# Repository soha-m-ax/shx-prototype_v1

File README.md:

# SHX // PROTOTYPE
### Designed by SohaMax // Solar Strike ⚡

The **SHX // PROTOTYPE** is a 6-keys & 1 rotary encloder macro pad designed for custom inputs.

---

## Visuals:

### 1. CAD View
The final assembly of the SHX PROTOTYPE keypad.

### 2. Schematic
The circuit diagram showing the XIAO RP2040 connected to the 7-key matrix.

### 3. PCB Layout
The custom 2-layer board design featuring hand-routed traces and mascot art.

---

## Bill of Materials (BOM):

| Component | Quantity | Purpose |
| :--- | :--- | :--- |
| **Seeed Studio XIAO RP2040** | 1 | Microcontroller |
| **Through-hole 1N4148 Diodes** | 7 | Signal Logic |
| **Mechanical Switches (MX-Style)** | 6 | Key Inputs |
| **EC11 Rotary Encoders** | 1 | Knob Inputs |
| **0.91 inch OLED Display** | 1 | Screen view |
| **DSA keycaps (White)** | 6 | Keycap Fit|
| **SK6812 MINI-E LEDs** | 7 | Custom lighting |
| **M3x16mm Screws** | 3 | | 3D Case Fiting |
| **M3x5mx4mm Heatset Inserts** | 3 | | 3D Case Fiting |
| **3D Printed Top Cover & Main Case** | Each 1 | Enclosure |

---

## Spec:

* **MCU:** XIAO RP2040.
* **Architecture:** 6 Mechanical Keys + 1 Rotary Encoder (Push-Button).
* **Firmware:** QMK (For now)
* **PCB Design:** KiCad 8.0.
* **CAD Design:** Fusion 360.

---

## Features:

The SHX // PROTOTYPE is configured with the following hardware & firmware capabilities:
* It's have  6 keys and 1 rotary encoder (press and rotate)
* It's have a display. At Starting it will show my branding and after some sec. it will show a bongocat, pressing a key make the cat's hand move (hope it work)
* Each key have each lights that can be glow brighter by pressing each key (each key make glow specific 1 light) and one exstra as side lighting...
---
> This firmware is not tested so i hope it will work... :-)

---

## Notes:
It will be nice to print all my 3d cash in yellow colour. (plz)

---

## Some bla bla:

I really happy to make this and also learned many things like codes etc for keyboard's farmware and also software like kicad, Fusion 360 etc. It's my first project with microcontroller. At first I couldn't understand anything but slow slow i learnet many more from internet. Hope everyone like it!
## Thanks hack club to give me a chance to show my skills and waiting! to make it real. I will make many more things!!...

 * {\\__/} 
* ( • . •) 
*  / >♥️

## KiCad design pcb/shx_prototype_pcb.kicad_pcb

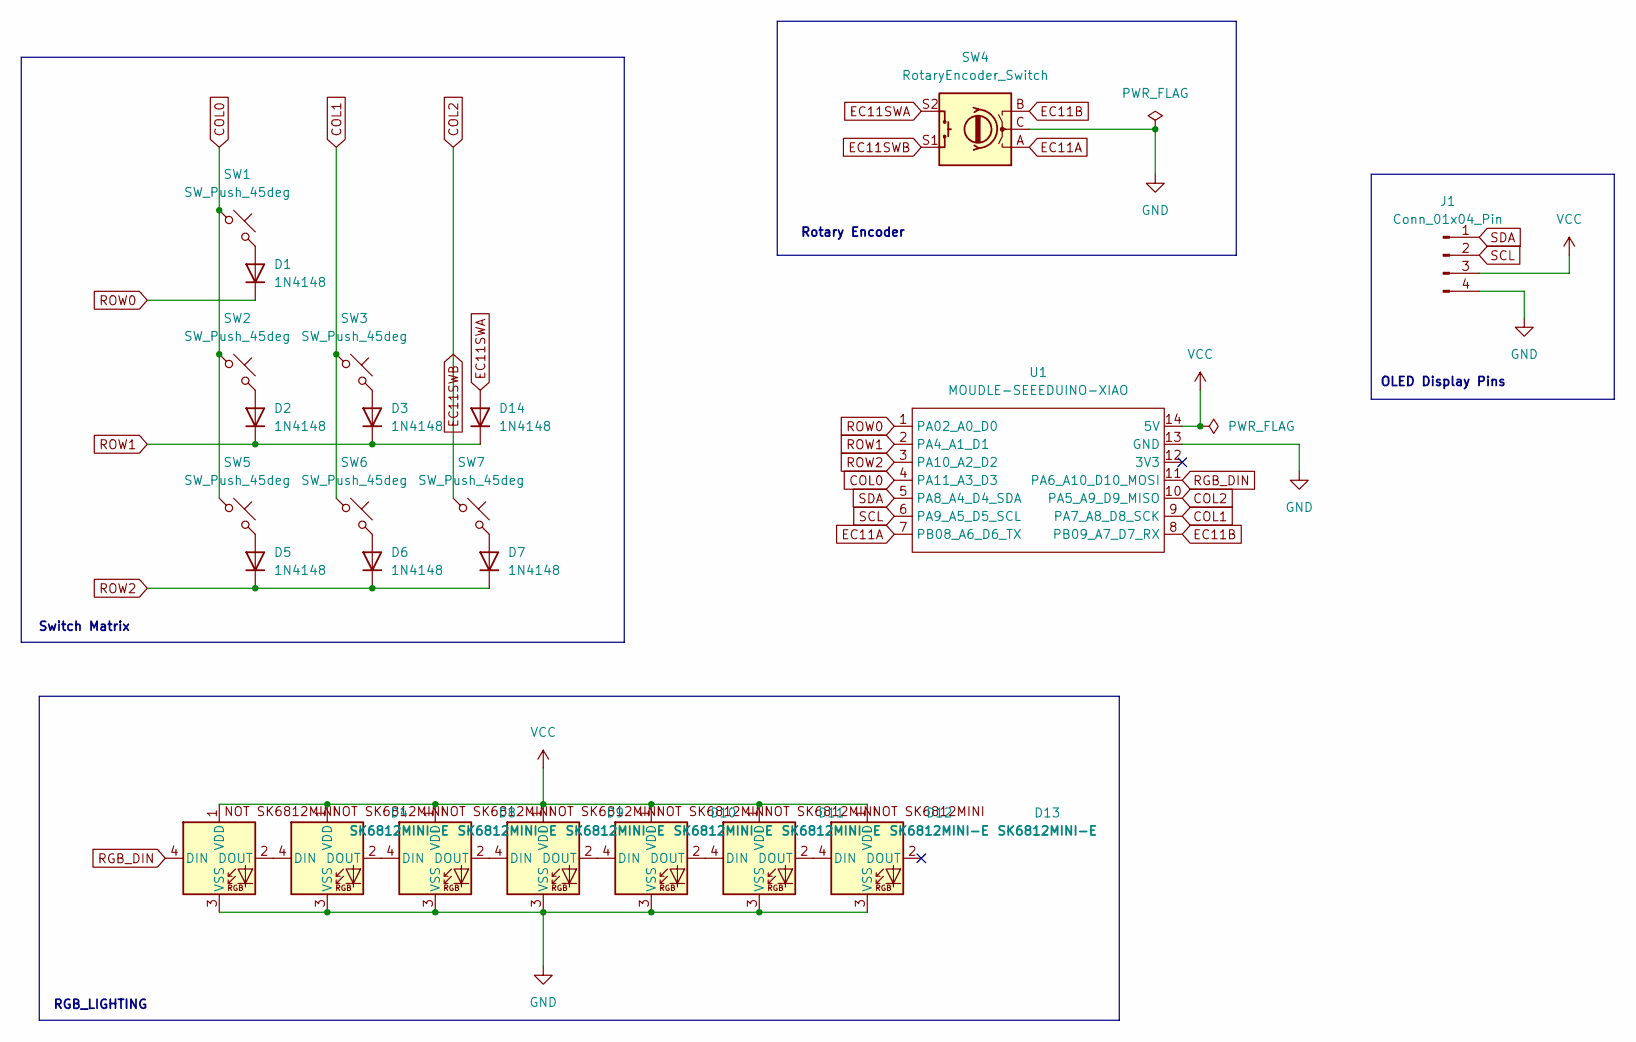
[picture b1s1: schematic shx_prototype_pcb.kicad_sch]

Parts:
D1, D2, D3, D5, D6, D7, D14: 1N4148; D_DO-35_SOD27_P7.62mm_Horizontal
D4, D8, D9, D10, D11, D12, D13: SK6812MINI-E; SK6812MINI-E_fixed
J1: Conn_01x04_Pin; PinSocket_1x04_P2.54mm_Vertical
SW1, SW2, SW3, SW5, SW6, SW7: SW_Push_45deg; SW_Cherry_MX_1.00u_PCB
SW4: RotaryEncoder_Switch; RotaryEncoder_Alps_EC11E-Switch_Vertical_H20mm
U1: MOUDLE-SEEEDUINO-XIAO; XIAO-Generic-Hybrid-14P-2.54-21X17.8MM

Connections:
COL0: SW1.1, SW2.1, SW5.1, U1.4 (PA11_A3_D3)
COL1: SW3.1, SW6.1, U1.9 (PA7_A8_D8_SCK)
COL2: SW4.S1, SW7.1, U1.10 (PA5_A9_D9_MISO)
EC11A: SW4.A, U1.7 (PB08_A6_D6_TX)
EC11B: SW4.B, U1.8 (PB09_A7_D7_RX)
EC11SWA: D14.2 (A), SW4.S2
GND: D4.3 (VSS), D8.3 (VSS), D9.3 (VSS), D10.3 (VSS), D11.3 (VSS), D12.3 (VSS), D13.3 (VSS), J1.4, SW4.C, U1.13 (GND)
unnamed: D1.2 (A), SW1.2
unnamed: D2.2 (A), SW2.2
unnamed: D3.2 (A), SW3.2
unnamed: D4.2 (DOUT), D8.4 (DIN)
unnamed: D5.2 (A), SW5.2
unnamed: D6.2 (A), SW6.2
unnamed: D7.2 (A), SW7.2
unnamed: D8.2 (DOUT), D9.4 (DIN)
unnamed: D9.2 (DOUT), D10.4 (DIN)
unnamed: D10.2 (DOUT), D11.4 (DIN)
unnamed: D11.2 (DOUT), D12.4 (DIN)
unnamed: D12.2 (DOUT), D13.4 (DIN)
RGB_DIN: D4.4 (DIN), U1.11 (PA6_A10_D10_MOSI)
ROW0: D1.1 (K), U1.1 (PA02_A0_D0)
ROW1: D2.1 (K), D3.1 (K), D14.1 (K), U1.2 (PA4_A1_D1)
ROW2: D5.1 (K), D6.1 (K), D7.1 (K), U1.3 (PA10_A2_D2)
SCL: J1.2, U1.6 (PA9_A5_D5_SCL)
SDA: J1.1, U1.5 (PA8_A4_D4_SDA)
VCC: D4.1 (VDD), D8.1 (VDD), D9.1 (VDD), D10.1 (VDD), D11.1 (VDD), D12.1 (VDD), D13.1 (VDD), J1.3, U1.14 (5V)

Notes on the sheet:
RGB_LIGHTING
OLED Display Pins
Rotary Encoder
Switch Matrix

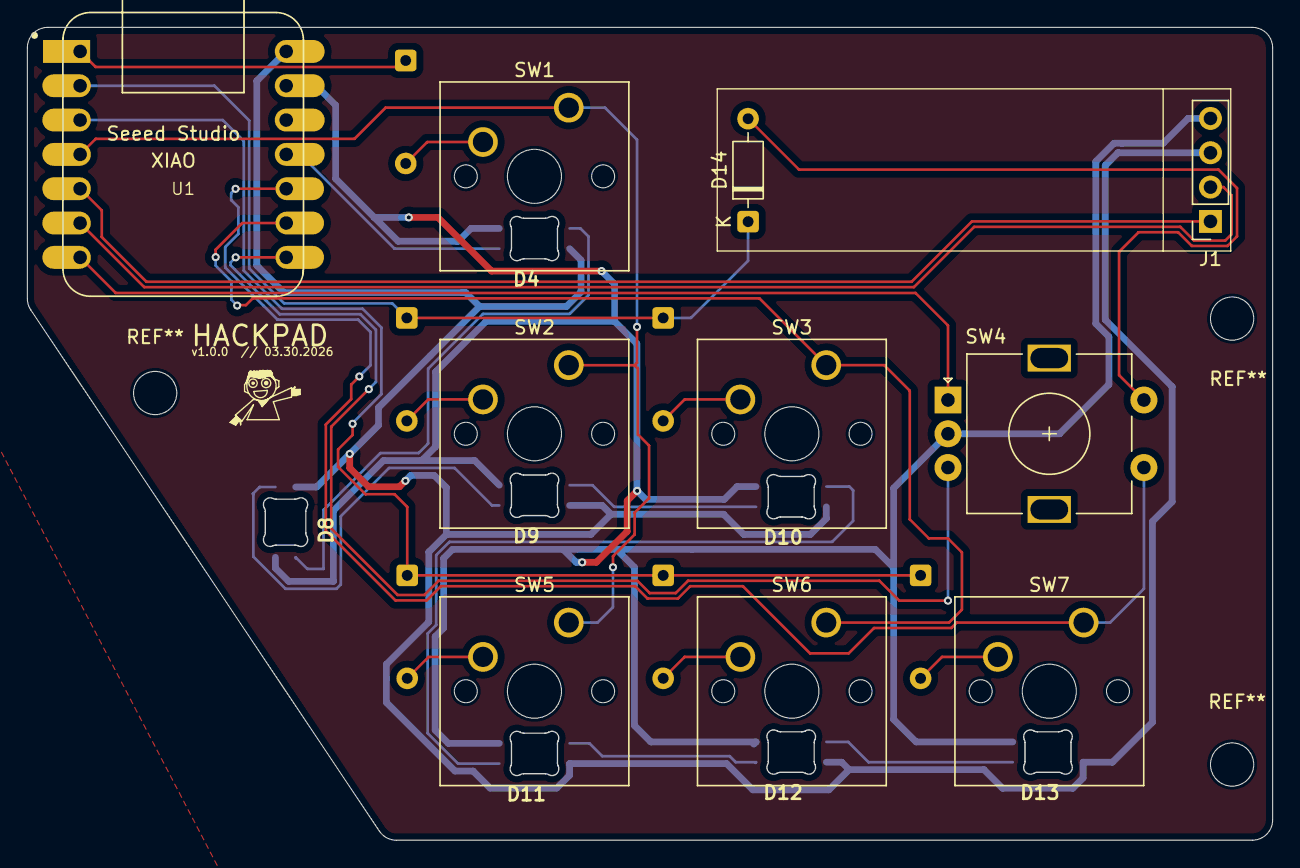
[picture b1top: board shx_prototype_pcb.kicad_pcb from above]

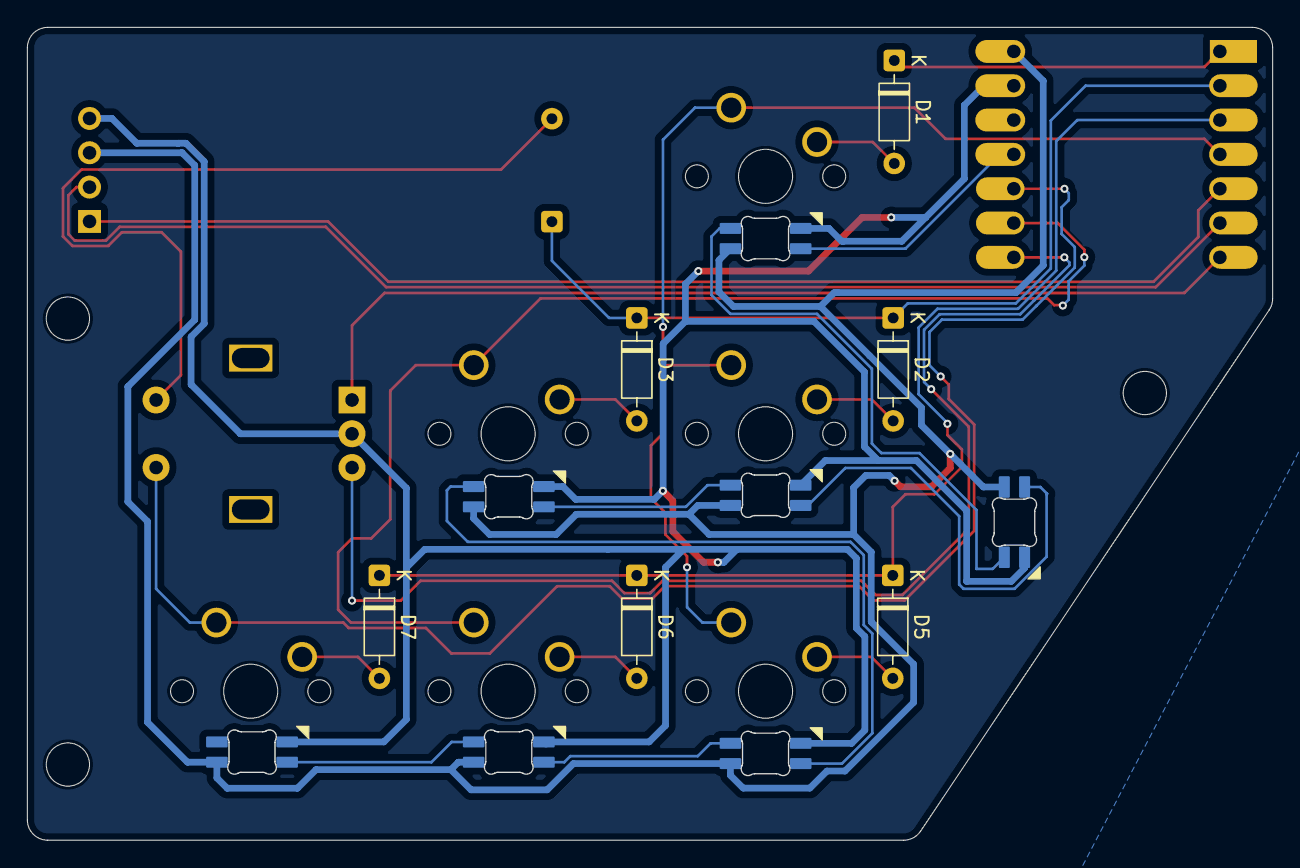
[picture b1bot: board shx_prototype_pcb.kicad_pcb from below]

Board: 2 copper layers, 92.1 x 60.1 mm, 23 parts (6 on the bottom side), 26 nets.

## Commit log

2026-03-31 Final SHX // PROTOTYPE Release
2026-03-31 SHX // PROTOTYPE
2026-03-31 Revise README for SHX prototype details
    Updated project description and specifications in README.
2026-03-31 Correct keycap fit capitalization in README
2026-03-31 Revise README section headers and formatting
    Updated section headers and improved formatting in README.
2026-03-31 Update features section to indicate upcoming changes
2026-03-31 Fix grammar in architecture description
2026-03-31 Update schematic image link in README
